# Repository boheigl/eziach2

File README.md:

# Eziach

A Steirische Harmonika (diatonic button accordion) without bellows, in two halves. A
**discant** (46 keys, right hand) and a **bass** (2 × 9 keys, left hand) plug together
through two load cells: the push and pull of the hands between the halves is measured
as force, **instead of bellows**. Every key is a Hall-effect key, read continuously, so
the firmware sets its own trigger points. The ESP32-S3 in the bass makes the sound
(earphone jack) and speaks MIDI over USB-C. For carrying, the discant turns over and
plugs onto the bass, keys inside.

Everything here is parametric source: OpenSCAD for the printed parts and the
assemblies, Python generating the KiCad boards.

## Videos

**The instrument:** force instead of bellows, the keys, playing, inside, plugging the
halves together and packing away (1 min). Click the preview for the full video.

**One key:** its parts, the assembly step by step, and the key pressed in section (1 min).

## Projects

| Folder | What |
|---|---|
| [`switch_hall/`](switch_hall/spec.md) | the key: a ground rod in a bronze bushing, magnet underneath, stock spring, O-ring stop; one source for discant and bass |
| [`discant/`](discant/spec.md) | right hand: one Hall board under 46 keys in four climbing rows, the tray housing, the cover with the thumb bar, the gauges' mount |
| [`bass/`](bass/spec.md) | left hand: 2 × 9 keys, hand plate and strap, battery, main board, the socket for the stored discant |
| [`assembly/`](assembly/spec.md) | both halves together, played and stored; the promo video |
| [`strain_gauge/`](strain_gauge/spec.md) | the load cells and their holders, the force path between the halves |
| [`hall_pcb/`](hall_pcb/spec.md) | the two key boards (DRV5055 per key, ADS7128 ADCs, NAU7802 for the gauges) |
| [`main_pcb/`](main_pcb/spec.md) | the main board: ESP32-S3, audio DAC, charger, 3.3 V supply |
| [`firmware/`](firmware/spec.md) | the ESP32-S3's firmware (ESP-IDF): Hall keys, load cells, the tuning table from the first eziach, TinySoundFont on the recorded Steirische to the earphone jack, USB-MIDI |
| [`contact_pcb/`](contact_pcb/spec.md) | spring-pin contacts that join power and I²C as the halves slide together |
| [`key_proto/`](key_proto/spec.md) | a test print: 2 rows of 4 keys on a board stand-in in the discant's tray, with the plate for a Bambu Lab X2D |
| [`thumb-bar/`](thumb-bar/profile.scad) | the discant's thumb bar profile |
| [`BOM.md`](BOM.md) | everything to buy, print or make for one instrument |
| [`TODO.md`](TODO.md) | open items |

## Building

```sh
make                    # switch_hall, discant, strain_gauge and key_proto into build/
make -C bass            # the bass and its 3D view
make -C assembly        # both halves together, build/assembly/view3d.html, and the
                        # illustrated assembly guide build/assembly/guide.html (assembly/guide/)
make -C key_proto       # the 8-key test print, build/key_proto/plate.3mf
make -C firmware/test   # the firmware's host tests (the firmware itself: idf.py build in firmware/)
make -C switch_hall video   # the key video (about half an hour)
make -C assembly promo      # the promo video (about an hour)
```

Needs OpenSCAD and Python 3; the boards need KiCad, the videos GStreamer. Everything
generated goes to `build/`, which is not under version control. Each `view3d.html` is a
single file with every part embedded, a 3D view that also works on a phone.

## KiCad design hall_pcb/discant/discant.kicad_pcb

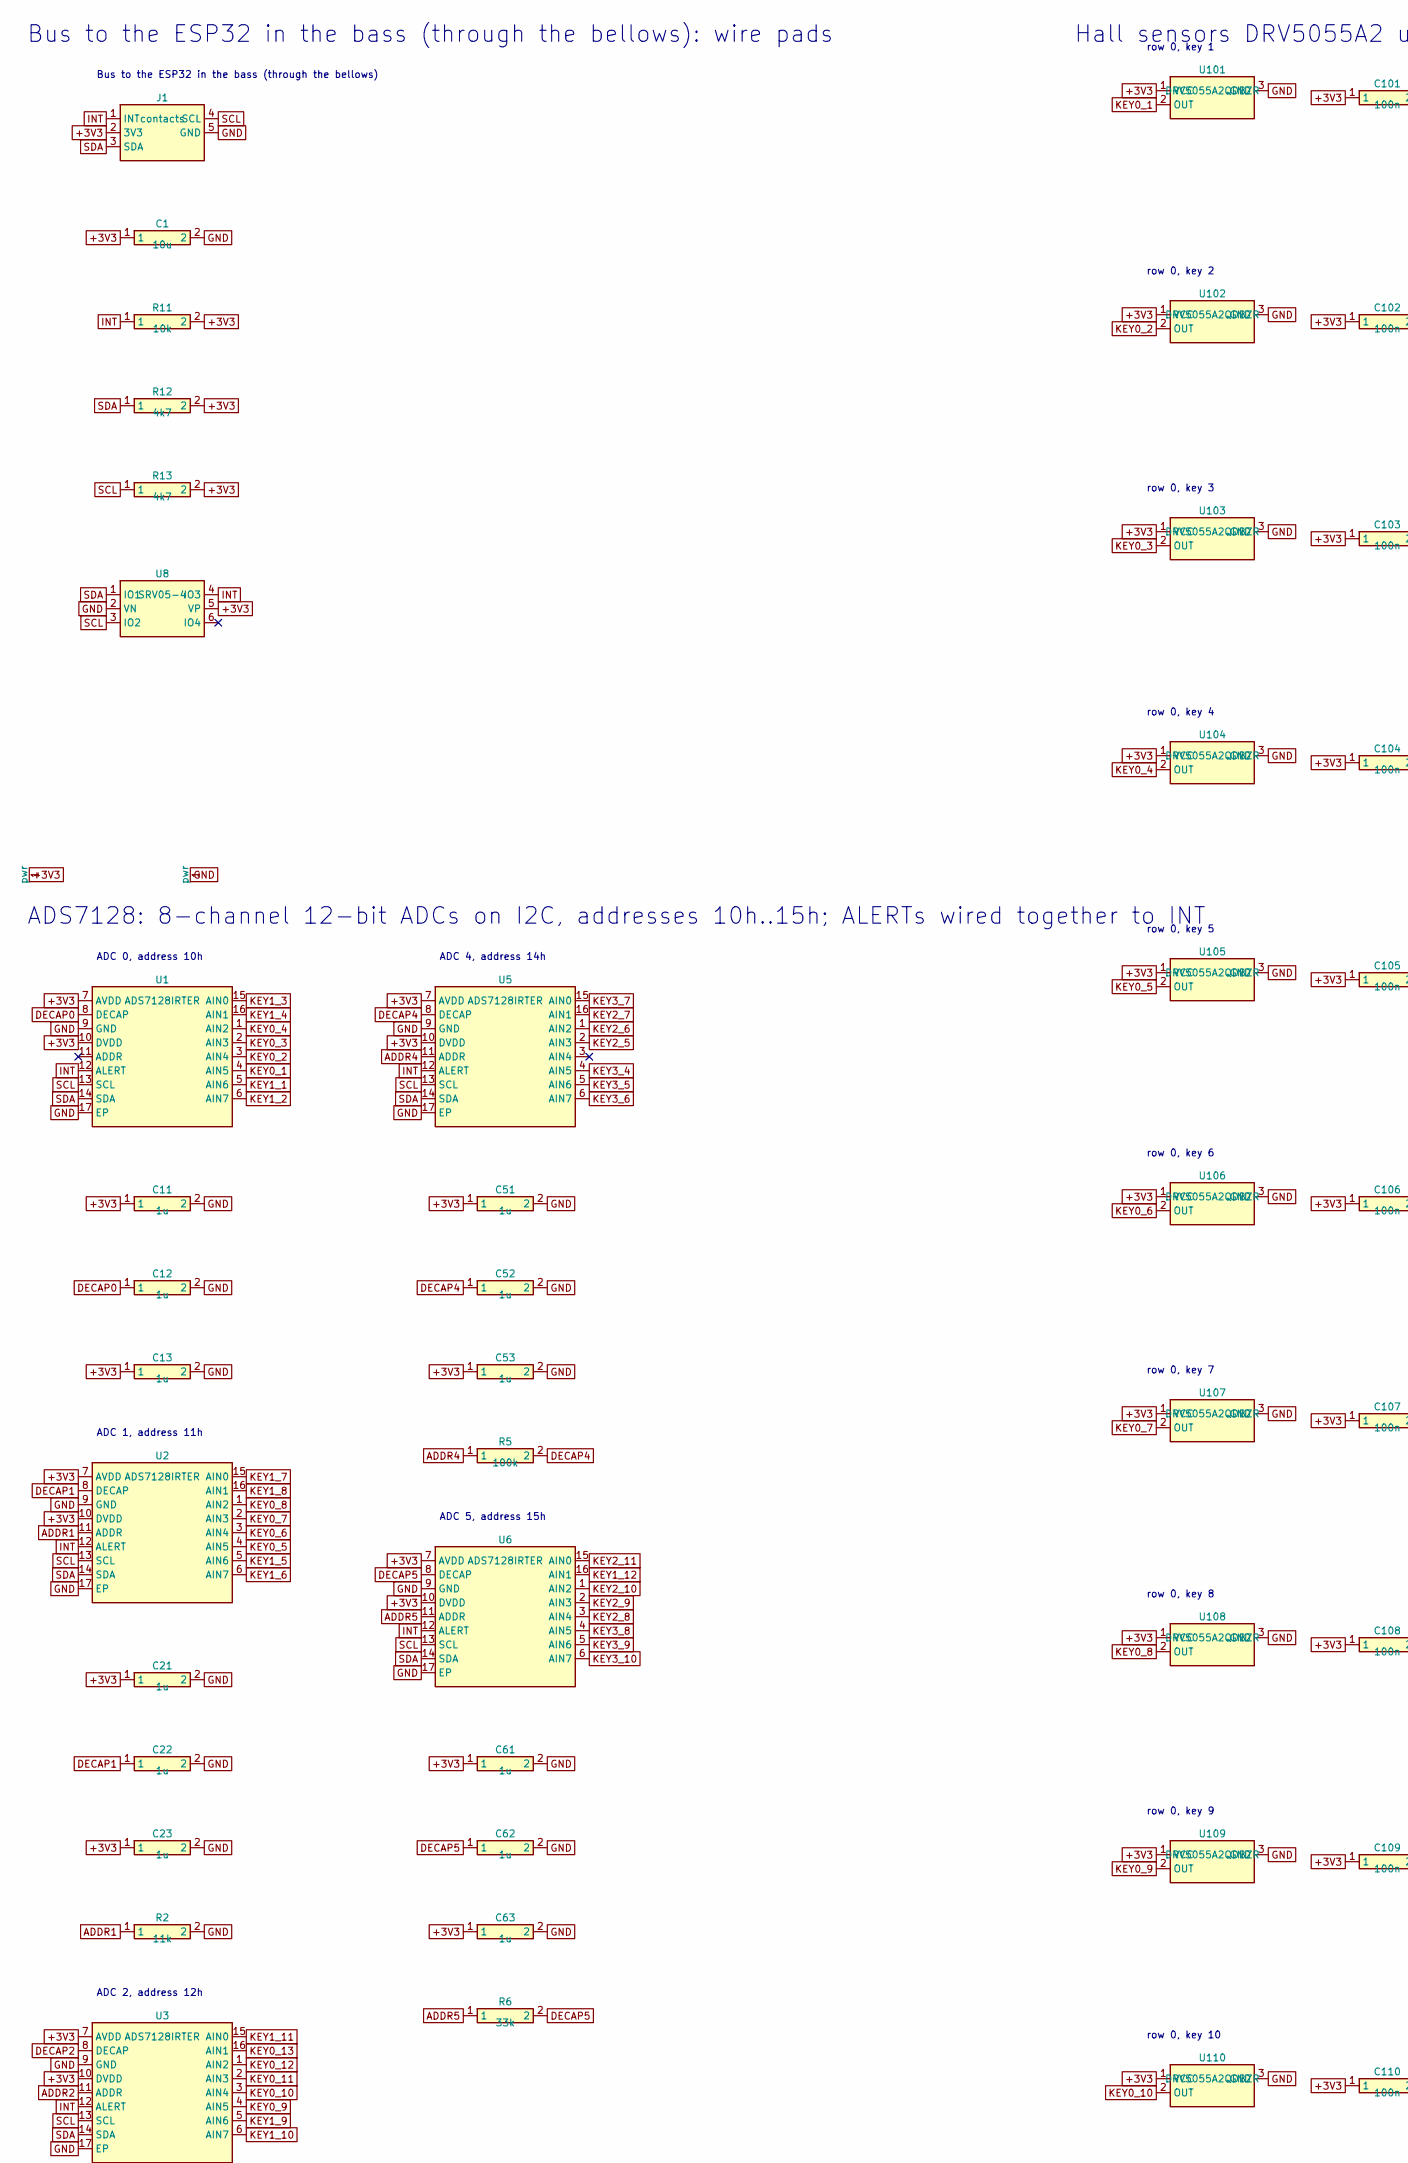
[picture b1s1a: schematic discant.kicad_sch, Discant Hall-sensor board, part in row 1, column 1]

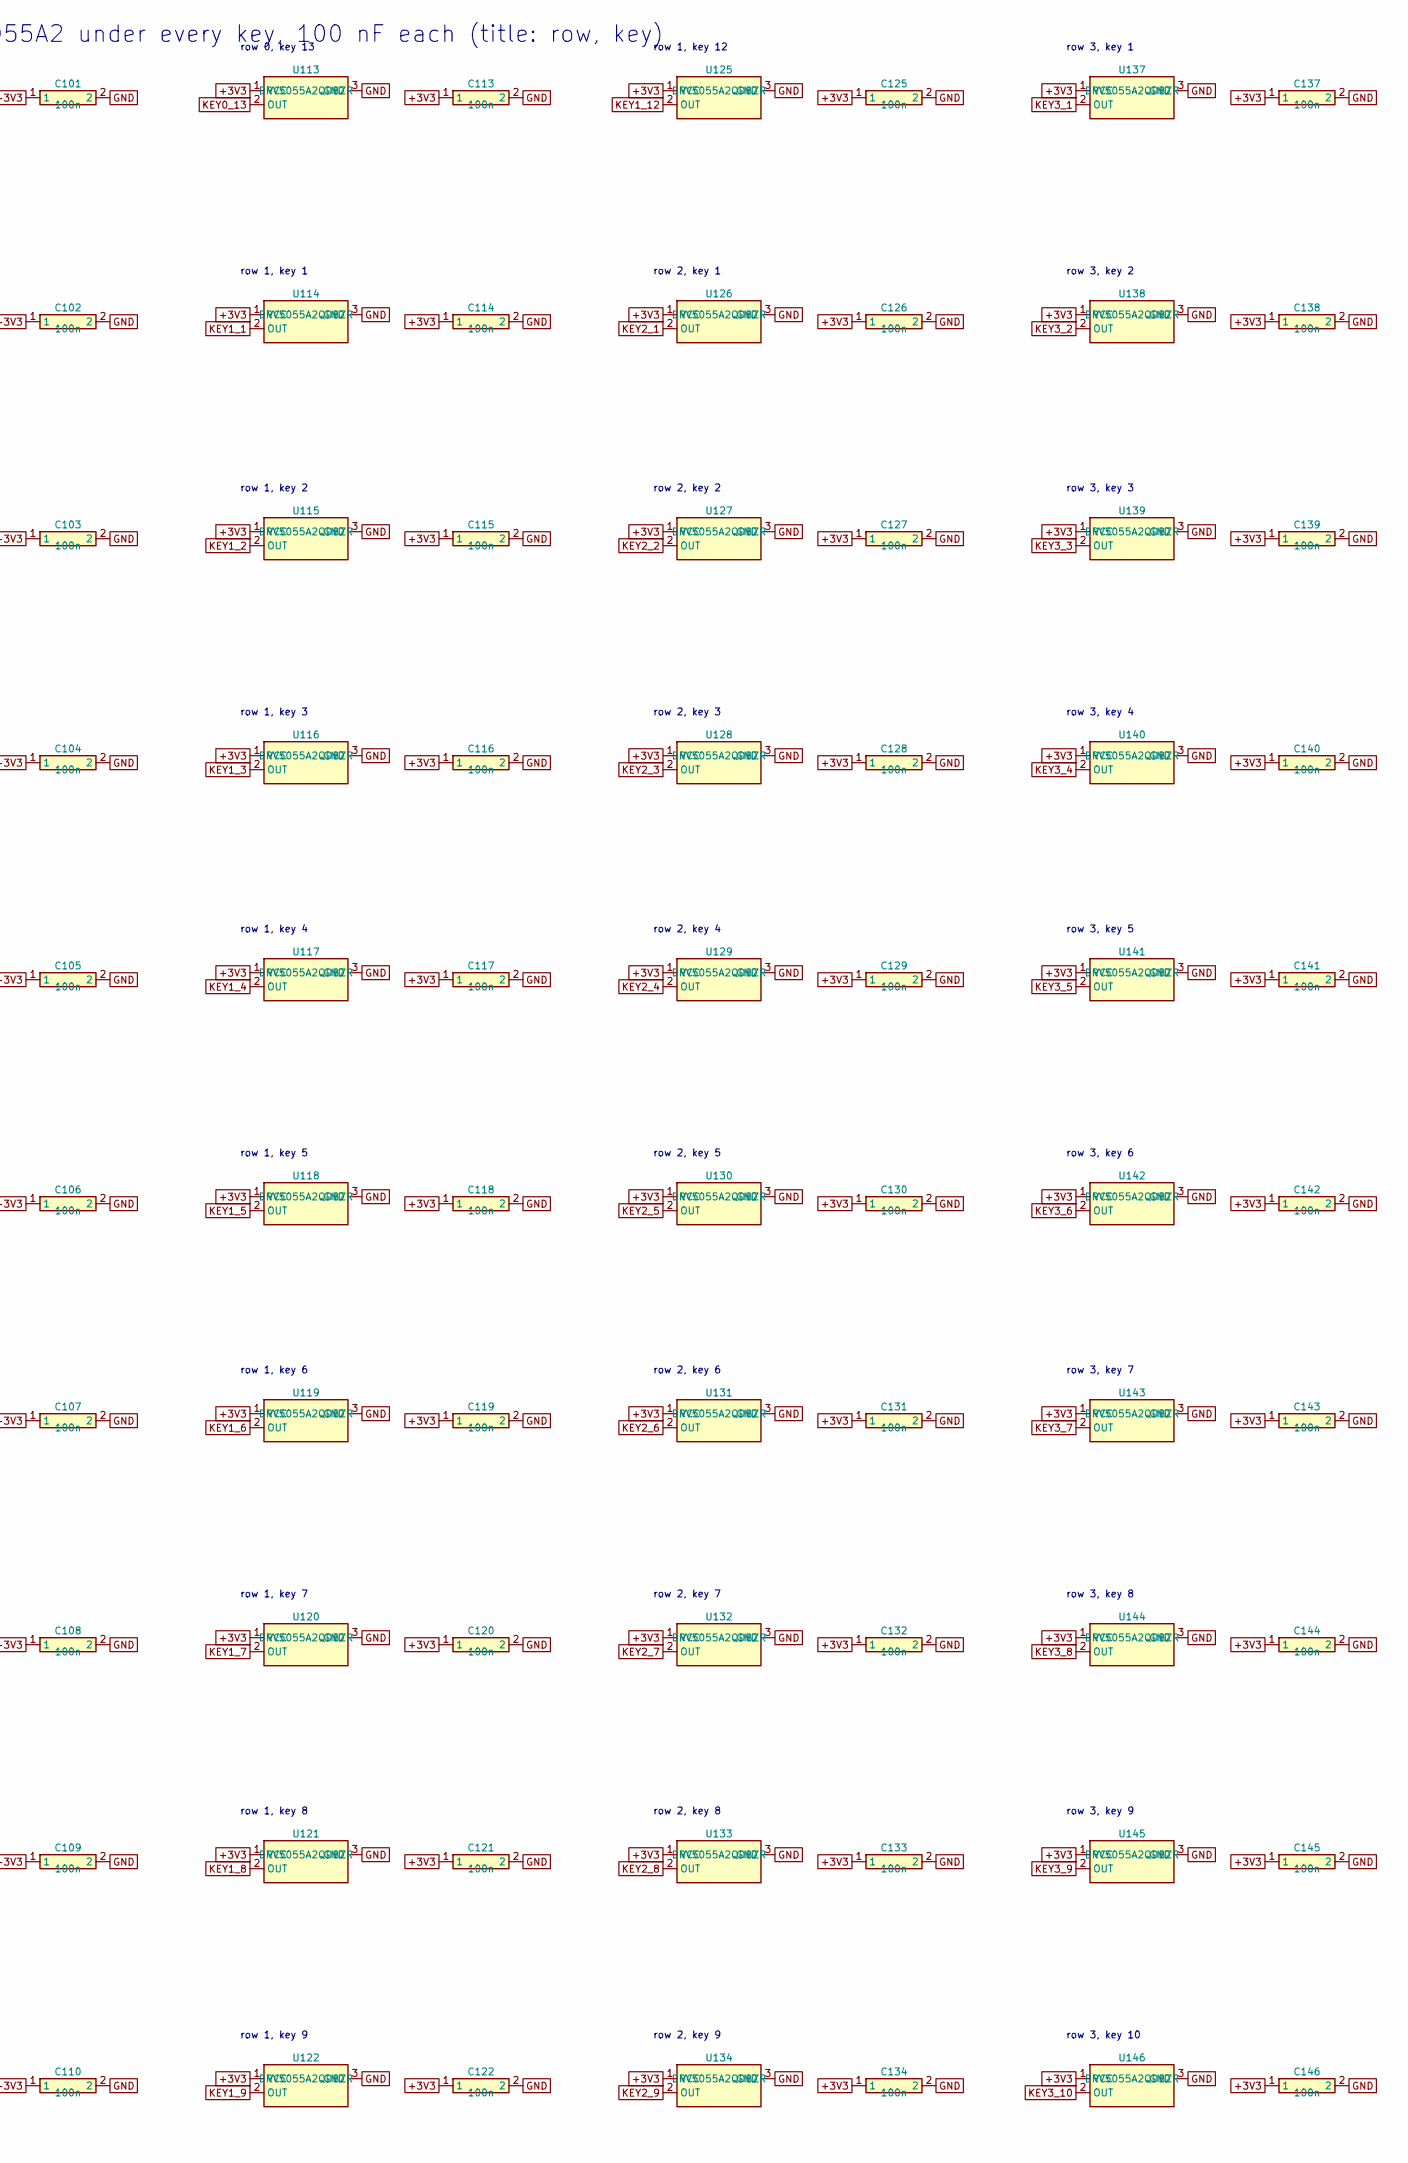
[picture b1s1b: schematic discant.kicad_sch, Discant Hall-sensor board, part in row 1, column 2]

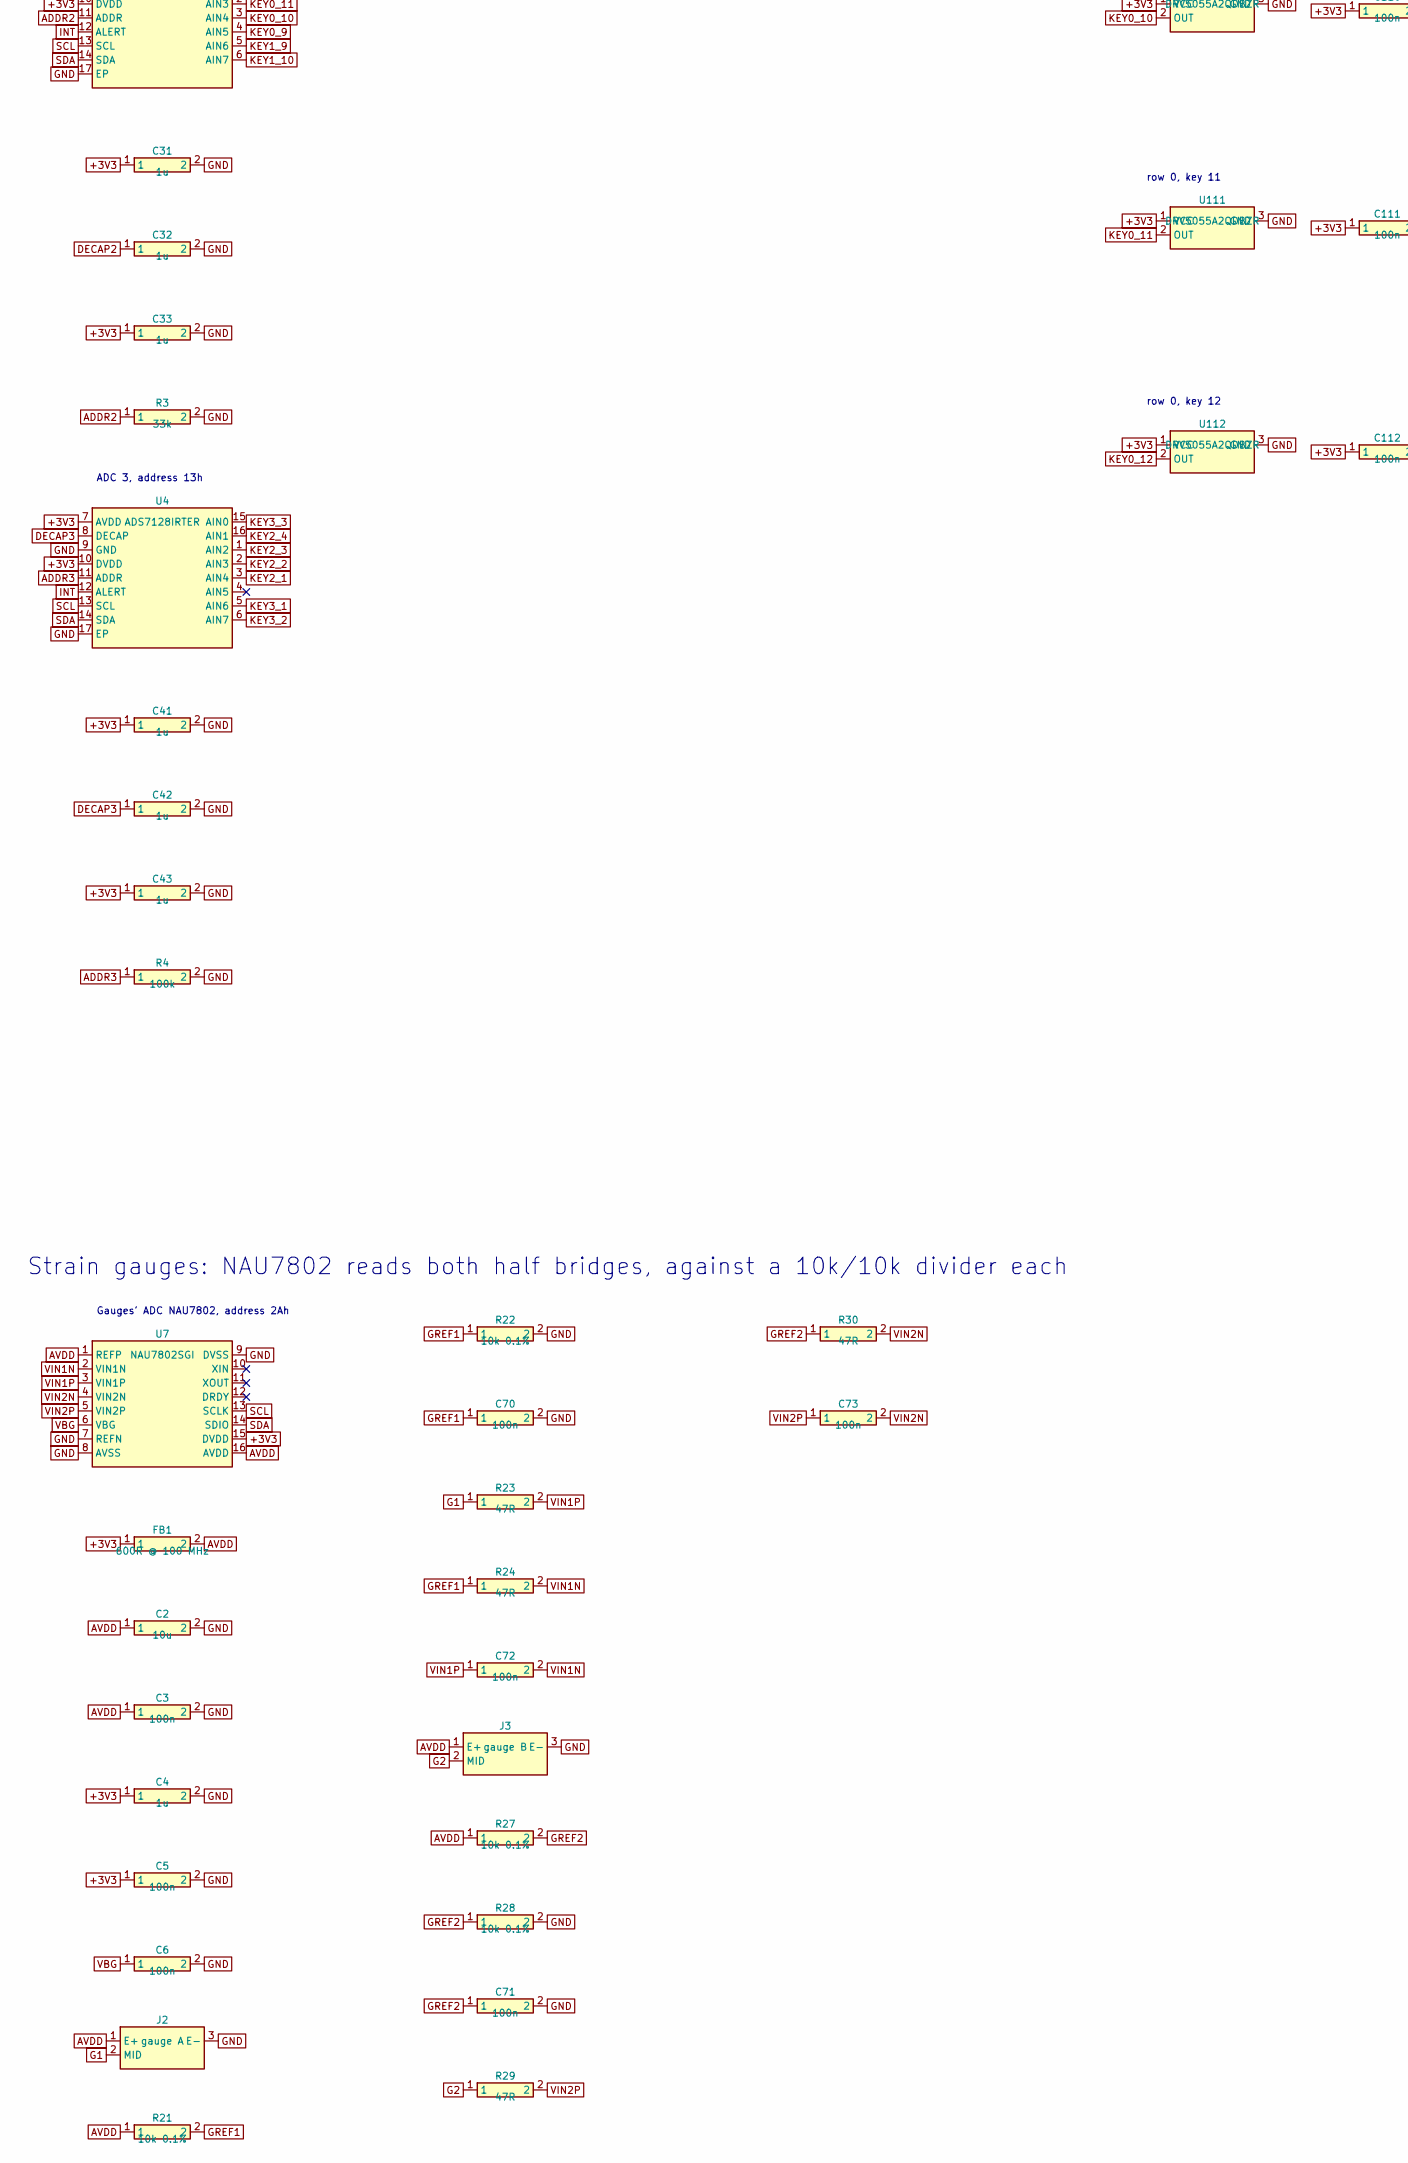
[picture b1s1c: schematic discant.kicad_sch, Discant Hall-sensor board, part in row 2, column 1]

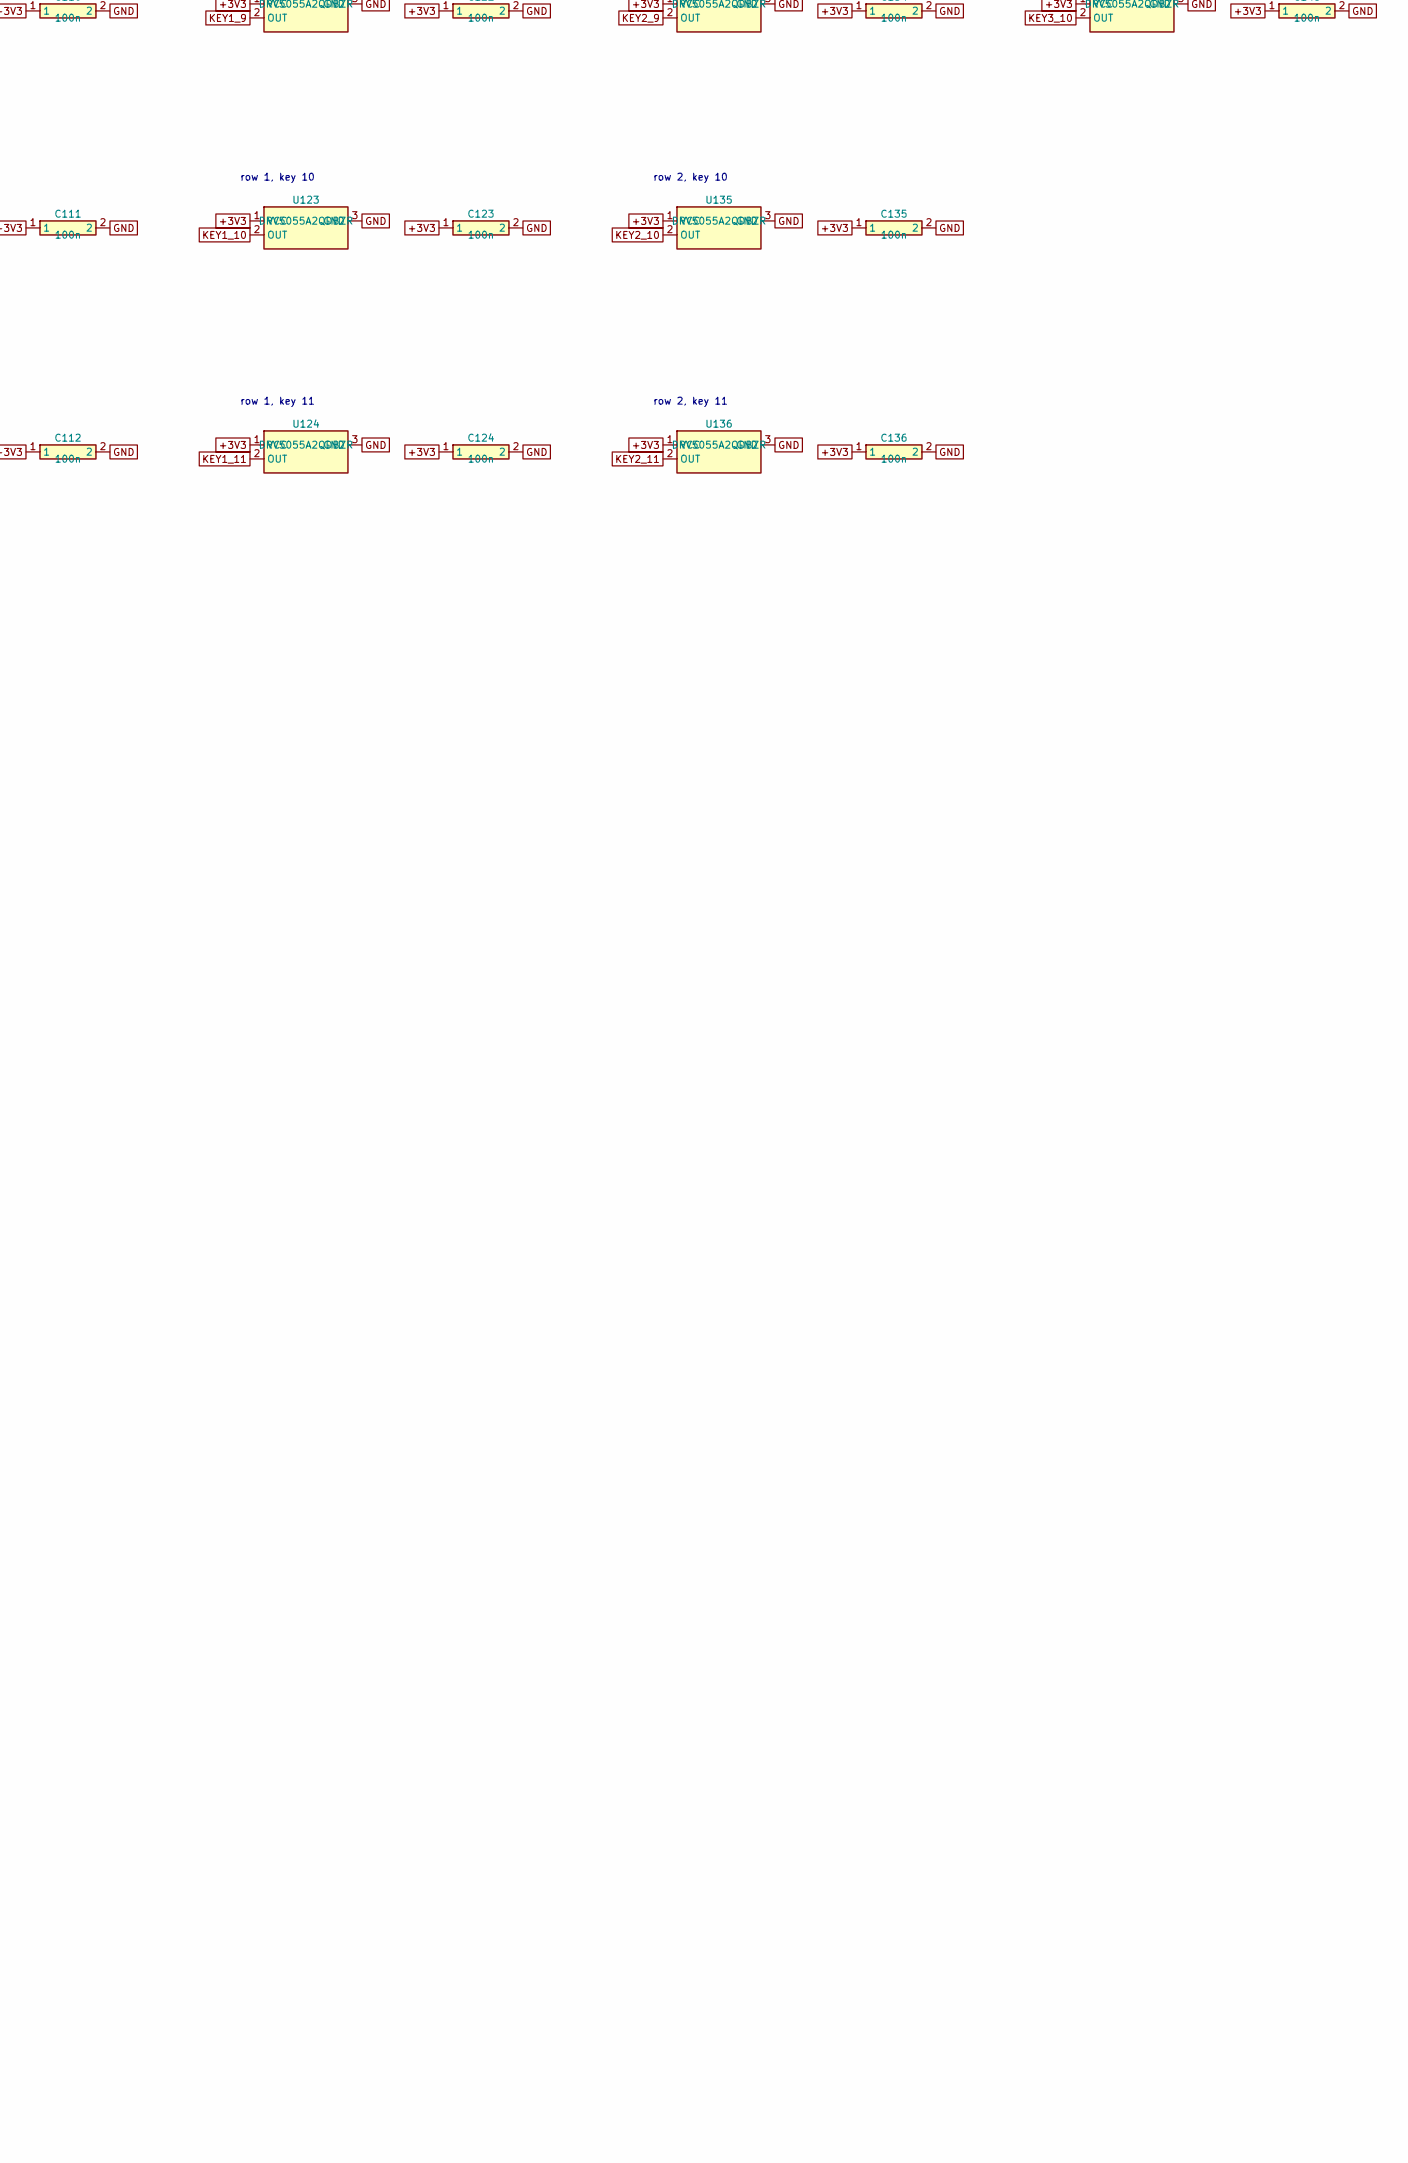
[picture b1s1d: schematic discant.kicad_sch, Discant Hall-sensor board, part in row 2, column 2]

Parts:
C1: 10u; C_0805_2012Metric; LCSC C15850
C2: 10u; C_0402_1005Metric; LCSC C15525
C3, C5, C6, C70, C71, C72, C73, C101, C102, C103, C104, C105, C106, C107, C108, C109, C110, C111, C112, C113, C114, C115, C116, C117, C118, C119, C120, C121, C122, C123, C124, C125, C126, C127, C128, C129, C130, C131, C132, C133, C134, C135, C136, C137, C138, C139, C140, C141, C142, C143, C144, C145, C146: 100n; C_0402_1005Metric; LCSC C1525
C4, C11, C12, C13, C21, C22, C23, C31, C32, C33, C41, C42, C43, C51, C52, C53, C61, C62, C63: 1u; C_0402_1005Metric; LCSC C52923
FB1: 600R @ 100 MHz; L_0402_1005Metric; LCSC C76884
J1: contacts; PinHeader_1x05_P2.00mm_Vertical
J2: gauge A; PinHeader_1x03_P2.00mm_Vertical
J3: gauge B; PinHeader_1x03_P2.00mm_Vertical
R2: 11k; R_0402_1005Metric; LCSC C25749
R3, R6: 33k; R_0402_1005Metric; LCSC C25779
R4, R5: 100k; R_0402_1005Metric; LCSC C25741
R11: 10k; R_0402_1005Metric; LCSC C25744
R12, R13: 4k7; R_0402_1005Metric; LCSC C25900
R21, R22, R27, R28: 10k 0.1%; R_0402_1005Metric; LCSC C190095
R23, R24, R29, R30: 47R; R_0402_1005Metric; LCSC C25118
U1, U2, U3, U4, U5, U6: ADS7128IRTER; WQFN-16-1EP_3x3mm_P0.5mm_EP1.68x1.68mm; LCSC C2867992
U7: NAU7802SGI; SOIC-16_3.9x9.9mm_P1.27mm; LCSC C2614351
U8: SRV05-4; SOT-23-6; LCSC C85364
U101, U102, U103, U104, U105, U106, U107, U108, U109, U110, U111, U112, U113, U114, U115, U116, U117, U118, U119, U120, U121, U122, U123, U124, U125, U126, U127, U128, U129, U130, U131, U132, U133, U134, U135, U136, U137, U138, U139, U140, U141, U142, U143, U144, U145, U146: DRV5055A2QDBZR; SOT-23; LCSC C266131

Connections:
+3V3: C1.1, C4.1, C5.1, C11.1, C13.1, C21.1, C23.1, C31.1, C33.1, C41.1, C43.1, C51.1, C53.1, C61.1, C63.1, C101.1, C102.1, C103.1, C104.1, C105.1, C106.1, C107.1, C108.1, C109.1, C110.1, C111.1, C112.1, C113.1, C114.1, C115.1, C116.1, C117.1, C118.1, C119.1, C120.1, C121.1, C122.1, C123.1, C124.1, C125.1, C126.1, C127.1, C128.1, C129.1, C130.1, C131.1, C132.1, C133.1, C134.1, C135.1, C136.1, C137.1, C138.1, C139.1, C140.1, C141.1, C142.1, C143.1, C144.1, C145.1, C146.1, FB1.1, J1.2 (3V3), R11.2, R12.2, R13.2, U1.7 (AVDD), U1.10 (DVDD), U2.7 (AVDD), U2.10 (DVDD), U3.7 (AVDD), U3.10 (DVDD), U4.7 (AVDD), U4.10 (DVDD), U5.7 (AVDD), U5.10 (DVDD), U6.7 (AVDD), U6.10 (DVDD), U7.15 (DVDD), U8.5 (VP), U101.1 (VCC), U102.1 (VCC), U103.1 (VCC), U104.1 (VCC), U105.1 (VCC), U106.1 (VCC), U107.1 (VCC), U108.1 (VCC), U109.1 (VCC), U110.1 (VCC), U111.1 (VCC), U112.1 (VCC), U113.1 (VCC), U114.1 (VCC), U115.1 (VCC), U116.1 (VCC), U117.1 (VCC), U118.1 (VCC), U119.1 (VCC), U120.1 (VCC), U121.1 (VCC), U122.1 (VCC), U123.1 (VCC), U124.1 (VCC), U125.1 (VCC), U126.1 (VCC), U127.1 (VCC), U128.1 (VCC), U129.1 (VCC), U130.1 (VCC), U131.1 (VCC), U132.1 (VCC), U133.1 (VCC), U134.1 (VCC), U135.1 (VCC), U136.1 (VCC), U137.1 (VCC), U138.1 (VCC), U139.1 (VCC), U140.1 (VCC), U141.1 (VCC), U142.1 (VCC), U143.1 (VCC), U144.1 (VCC), U145.1 (VCC), U146.1 (VCC)
ADDR1: R2.1, U2.11 (ADDR)
ADDR2: R3.1, U3.11 (ADDR)
ADDR3: R4.1, U4.11 (ADDR)
ADDR4: R5.1, U5.11 (ADDR)
ADDR5: R6.1, U6.11 (ADDR)
AVDD: C2.1, C3.1, FB1.2, J2.1 (E+), J3.1 (E+), R21.1, R27.1, U7.1 (REFP), U7.16 (AVDD)
DECAP0: C12.1, U1.8 (DECAP)
DECAP1: C22.1, U2.8 (DECAP)
DECAP2: C32.1, U3.8 (DECAP)
DECAP3: C42.1, U4.8 (DECAP)
DECAP4: C52.1, R5.2, U5.8 (DECAP)
DECAP5: C62.1, R6.2, U6.8 (DECAP)
G1: J2.2 (MID), R23.1
G2: J3.2 (MID), R29.1
GND: C1.2, C2.2, C3.2, C4.2, C5.2, C6.2, C11.2, C12.2, C13.2, C21.2, C22.2, C23.2, C31.2, C32.2, C33.2, C41.2, C42.2, C43.2, C51.2, C52.2, C53.2, C61.2, C62.2, C63.2, C70.2, C71.2, C101.2, C102.2, C103.2, C104.2, C105.2, C106.2, C107.2, C108.2, C109.2, C110.2, C111.2, C112.2, C113.2, C114.2, C115.2, C116.2, C117.2, C118.2, C119.2, C120.2, C121.2, C122.2, C123.2, C124.2, C125.2, C126.2, C127.2, C128.2, C129.2, C130.2, C131.2, C132.2, C133.2, C134.2, C135.2, C136.2, C137.2, C138.2, C139.2, C140.2, C141.2, C142.2, C143.2, C144.2, C145.2, C146.2, J1.5 (GND), J2.3 (E-), J3.3 (E-), R2.2, R3.2, R4.2, R22.2, R28.2, U1.9 (GND), U1.17 (EP), U2.9 (GND), U2.17 (EP), U3.9 (GND), U3.17 (EP), U4.9 (GND), U4.17 (EP), U5.9 (GND), U5.17 (EP), U6.9 (GND), U6.17 (EP), U7.7 (REFN), U7.8 (AVSS), U7.9 (DVSS), U8.2 (VN), U101.3 (GND), U102.3 (GND), U103.3 (GND), U104.3 (GND), U105.3 (GND), U106.3 (GND), U107.3 (GND), U108.3 (GND), U109.3 (GND), U110.3 (GND), U111.3 (GND), U112.3 (GND), U113.3 (GND), U114.3 (GND), U115.3 (GND), U116.3 (GND), U117.3 (GND), U118.3 (GND), U119.3 (GND), U120.3 (GND), U121.3 (GND), U122.3 (GND), U123.3 (GND), U124.3 (GND), U125.3 (GND), U126.3 (GND), U127.3 (GND), U128.3 (GND), U129.3 (GND), U130.3 (GND), U131.3 (GND), U132.3 (GND), U133.3 (GND), U134.3 (GND), U135.3 (GND), U136.3 (GND), U137.3 (GND), U138.3 (GND), U139.3 (GND), U140.3 (GND), U141.3 (GND), U142.3 (GND), U143.3 (GND), U144.3 (GND), U145.3 (GND), U146.3 (GND)
GREF1: C70.1, R21.2, R22.1, R24.1
GREF2: C71.1, R27.2, R28.1, R30.1
INT: J1.1 (INT), R11.1, U1.12 (ALERT), U2.12 (ALERT), U3.12 (ALERT), U4.12 (ALERT), U5.12 (ALERT), U6.12 (ALERT), U8.4 (IO3)
KEY0_1: U1.4 (AIN5), U101.2 (OUT)
KEY0_2: U1.3 (AIN4), U102.2 (OUT)
KEY0_3: U1.2 (AIN3), U103.2 (OUT)
KEY0_4: U1.1 (AIN2), U104.2 (OUT)
KEY0_5: U2.4 (AIN5), U105.2 (OUT)
KEY0_6: U2.3 (AIN4), U106.2 (OUT)
KEY0_7: U2.2 (AIN3), U107.2 (OUT)
KEY0_8: U2.1 (AIN2), U108.2 (OUT)
KEY0_9: U3.4 (AIN5), U109.2 (OUT)
KEY0_10: U3.3 (AIN4), U110.2 (OUT)
KEY0_11: U3.2 (AIN3), U111.2 (OUT)
KEY0_12: U3.1 (AIN2), U112.2 (OUT)
KEY0_13: U3.16 (AIN1), U113.2 (OUT)
KEY1_1: U1.5 (AIN6), U114.2 (OUT)
KEY1_2: U1.6 (AIN7), U115.2 (OUT)
KEY1_3: U1.15 (AIN0), U116.2 (OUT)
KEY1_4: U1.16 (AIN1), U117.2 (OUT)
KEY1_5: U2.5 (AIN6), U118.2 (OUT)
KEY1_6: U2.6 (AIN7), U119.2 (OUT)
KEY1_7: U2.15 (AIN0), U120.2 (OUT)
KEY1_8: U2.16 (AIN1), U121.2 (OUT)
KEY1_9: U3.5 (AIN6), U122.2 (OUT)
KEY1_10: U3.6 (AIN7), U123.2 (OUT)
KEY1_11: U3.15 (AIN0), U124.2 (OUT)
KEY1_12: U6.16 (AIN1), U125.2 (OUT)
KEY2_1: U4.3 (AIN4), U126.2 (OUT)
KEY2_2: U4.2 (AIN3), U127.2 (OUT)
KEY2_3: U4.1 (AIN2), U128.2 (OUT)
KEY2_4: U4.16 (AIN1), U129.2 (OUT)
KEY2_5: U5.2 (AIN3), U130.2 (OUT)
KEY2_6: U5.1 (AIN2), U131.2 (OUT)
KEY2_7: U5.16 (AIN1), U132.2 (OUT)
KEY2_8: U6.3 (AIN4), U133.2 (OUT)
KEY2_9: U6.2 (AIN3), U134.2 (OUT)
KEY2_10: U6.1 (AIN2), U135.2 (OUT)
KEY2_11: U6.15 (AIN0), U136.2 (OUT)
KEY3_1: U4.5 (AIN6), U137.2 (OUT)
KEY3_2: U4.6 (AIN7), U138.2 (OUT)
KEY3_3: U4.15 (AIN0), U139.2 (OUT)
KEY3_4: U5.4 (AIN5), U140.2 (OUT)
KEY3_5: U5.5 (AIN6), U141.2 (OUT)
KEY3_6: U5.6 (AIN7), U142.2 (OUT)
KEY3_7: U5.15 (AIN0), U143.2 (OUT)
KEY3_8: U6.4 (AIN5), U144.2 (OUT)
KEY3_9: U6.5 (AIN6), U145.2 (OUT)
KEY3_10: U6.6 (AIN7), U146.2 (OUT)
SCL: J1.4 (SCL), R13.1, U1.13 (SCL), U2.13 (SCL), U3.13 (SCL), U4.13 (SCL), U5.13 (SCL), U6.13 (SCL), U7.13 (SCLK), U8.3 (IO2)
SDA: J1.3 (SDA), R12.1, U1.14 (SDA), U2.14 (SDA), U3.14 (SDA), U4.14 (SDA), U5.14 (SDA), U6.14 (SDA), U7.14 (SDIO), U8.1 (IO1)
VBG: C6.1, U7.6 (VBG)
VIN1N: C72.2, R24.2, U7.2 (VIN1N)
VIN1P: C72.1, R23.2, U7.3 (VIN1P)
VIN2N: C73.2, R30.2, U7.4 (VIN2N)
VIN2P: C73.1, R29.2, U7.5 (VIN2P)

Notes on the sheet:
Bus to the ESP32 in the bass (through the bellows): wire pads
Bus to the ESP32 in the bass (through the bellows)
ADS7128: 8-channel 12-bit ADCs on I2C, addresses 10h..15h; ALERTs wired together to INT
ADC 0, address 10h
ADC 1, address 11h
ADC 2, address 12h
ADC 3, address 13h
ADC 4, address 14h
ADC 5, address 15h
Hall sensors DRV5055A2 under every key, 100 nF each (title: row, key)
row 0, key 1
row 0, key 2
row 0, key 3
row 0, key 4
row 0, key 5
row 0, key 6
row 0, key 7
row 0, key 8
row 0, key 9
row 0, key 10
row 0, key 11
row 0, key 12
row 0, key 13
row 1, key 1
row 1, key 2
row 1, key 3
row 1, key 4
row 1, key 5
row 1, key 6
row 1, key 7
row 1, key 8
row 1, key 9
row 1, key 10
row 1, key 11
row 1, key 12
row 2, key 1
row 2, key 2
row 2, key 3
row 2, key 4
row 2, key 5

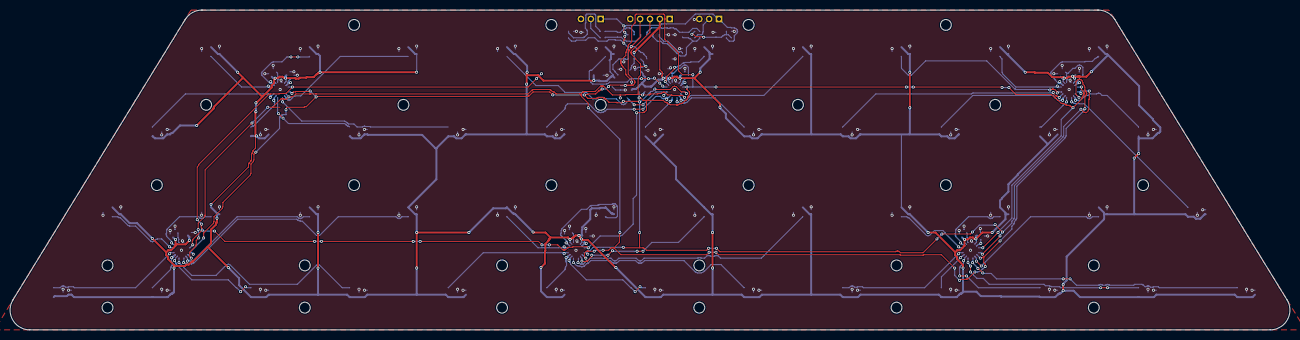
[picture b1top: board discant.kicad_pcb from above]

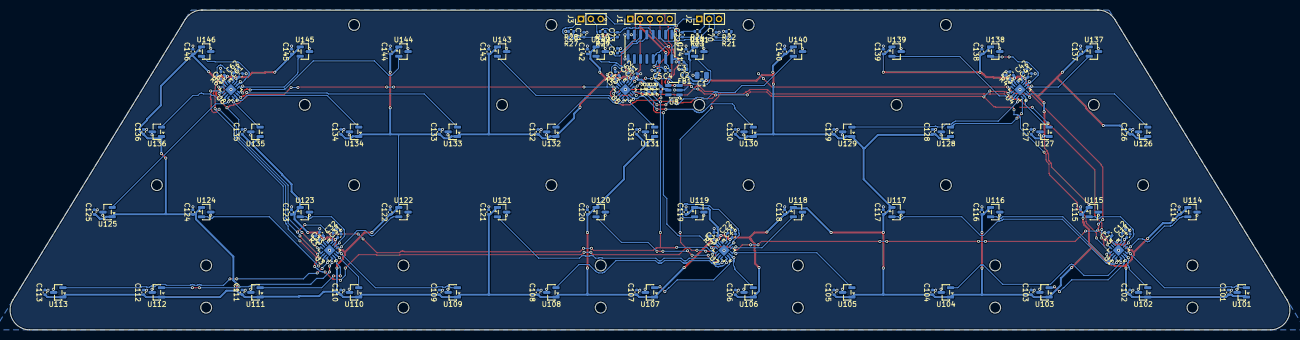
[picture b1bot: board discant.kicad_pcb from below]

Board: 2 copper layers, 259.5 x 64.8 mm, 148 parts (148 on the bottom side), 72 nets.

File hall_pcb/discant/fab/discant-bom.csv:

"Comment","Designator","Footprint","LCSC","Quantity"
"10u","C1","Capacitor_SMD:C_0805_2012Metric","C15850","1"
"10u","C2","Capacitor_SMD:C_0402_1005Metric","C15525","1"
"100n","C3,C5,C6,C70,C71,C72,C73,C101,C102,C103,C104,C105,C106,C107,C108,C109,C110,C111,C112,C113,C114,C115,C116,C117,C118,C119,C120,C121,C122,C123,C124,C125,C126,C127,C128,C129,C130,C131,C132,C133,C134,C135,C136,C137,C138,C139,C140,C141,C142,C143,C144,C145,C146","Capacitor_SMD:C_0402_1005Metric","C1525","53"
"1u","C4,C11,C12,C13,C21,C22,C23,C31,C32,C33,C41,C42,C43,C51,C52,C53,C61,C62,C63","Capacitor_SMD:C_0402_1005Metric","C52923","19"
"600R @ 100 MHz","FB1","Inductor_SMD:L_0402_1005Metric","C76884","1"
"11k","R2","Resistor_SMD:R_0402_1005Metric","C25749","1"
"10k","R11","Resistor_SMD:R_0402_1005Metric","C25744","1"
"4k7","R12,R13","Resistor_SMD:R_0402_1005Metric","C25900","2"
"10k 0.1%","R21,R22,R27,R28","Resistor_SMD:R_0402_1005Metric","C190095","4"
"47R","R23,R24,R29,R30","Resistor_SMD:R_0402_1005Metric","C25118","4"
"33k","R3,R6","Resistor_SMD:R_0402_1005Metric","C25779","2"
"100k","R4,R5","Resistor_SMD:R_0402_1005Metric","C25741","2"
"NAU7802SGI","U7","Package_SO:SOIC-16_3.9x9.9mm_P1.27mm","C2614351","1"
"SRV05-4","U8","Package_TO_SOT_SMD:SOT-23-6","C85364","1"
"ADS7128IRTER","U1,U2,U3,U4,U5,U6","Package_DFN_QFN:WQFN-16-1EP_3x3mm_P0.5mm_EP1.68x1.68mm","C2867992","6"
"DRV5055A2QDBZR","U101,U102,U103,U104,U105,U106,U107,U108,U109,U110,U111,U112,U113,U114,U115,U116,U117,U118,U119,U120,U121,U122,U123,U124,U125,U126,U127,U128,U129,U130,U131,U132,U133,U134,U135,U136,U137,U138,U139,U140,U141,U142,U143,U144,U145,U146","Package_TO_SOT_SMD:SOT-23","C266131","46"
